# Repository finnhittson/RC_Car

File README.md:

# 9V Battery Power RC Car
This repo documents how to make an RC car and transmitter using 3D printted parts, a PIC16LF18325 microcontroller, nRF24L01 RF modules, a 9V battery to power the car and the transmitter, and other basic hardware components.

Table of contents:  
1. [Design Overview](##design-overview)
2. [Software](###software)
3. [Electrical](###electrical)
4. [Bill of Materials](##bill-of-materials)
## Design Overview
The three main components in building this car are the software, electrical, and the mechanical aspect of the car and controller. The following sections talks about each of these parts in detail.

### Software
Using the PIC16LF18326 as the microcontroller, the driver code was written exclusively in C. The driver code was programmed onto the PIC16 using the MPLAB SNAP and the MPLABX IDE. The software components are broken into the following three files:
1. `main.c`: runs main finite state machine responsible for executing high level transmitter/receiver instructions for controlling motors and servos for the receiver and reading analog control inputs for the trasmitter.
2. `spi.c`: helper SPI functions for transmitting and receiving messages to and from the nRF24L01 radio module.
3. `nRF24L01.c`: helper functions for configuring the nRF24L01 radio module using the `spi.c` functons.

Because this project is intended to be a workshop only one version of code or `main.c` file is written for simplicity. Therefore, for the `main.c` to differentiate between running transmitter code and receiver, a GPIO pin on the micro is dedicated for this indication. The pin under questions is RA5 (pin 2) from the tables below which descripe the pinout for the PIC16 in both the receiver and transmitter. If RA5 is pulled high, then the `main.c` executes transmitter code only. Similarly if RA5 is pulled low, then the `main.c` only executes receiver code. 

| Transmitter Pin Description |             |                |                 | | | Receiver Pin Description    |             |                |                 |
|-----------------------------|-------------|----------------|-----------------|-|-|-----------------------------|-------------|----------------|-----------------|
| **Pin Number**              | **Port**    | **Net Name**   | **Notes**       | | | **Pin Number**              | **Port**    | **Net Name**   | **Notes**       |
| 1                           | $V_{DD}$    | 3.3V           | power supply    | | | 1                           | $V_{DD}$    | 3.3V           | power supply    |
| 2                           | RA5         | 3.3V           | type select     | | | 2                           | RA5         | GND            | type select     |
| 3                           | RA4         | CSN            | SPI bus         | | | 3                           | RA4         | CSN            | SPI bus         |
| 4                           | RA3         | MCLR           | program/NC      | | | 4                           | RA3         | MCLR           | program/NC      |
| 5                           | RC5         | MOSI           | SPI bus         | | | 5                           | RC5         | CE             | radio enable    |
| 6                           | RC4         | SPEED          | pot input       | | | 6                           | RC4         | PWM5.1         | motor PWM       |
| 7                           | RC3         | STEER          | pot input       | | | 7                           | RC3         | PWM6           | servo PWM       |
|                             |             |                |                 | | |                             |             |                |                 |
| 8                           | RC2         | IRQ            | radio interrupt | | | 8                           | RC2         | PWM5           | motor PWM       |
| 9                           | RC1         | MISO           | SPI bus         | | | 9                           | RC1         | MISO           | SPI bus         |
| 10                          | RC0         | SCK            | SPI bus         | | | 10                          | RC0         | SCK            | SPI bus         |
| 11                          | RA2         | CE             | radio enable    | | | 11                          | RA2         | MOSI           | SPI bus         |
| 12                          | RA1         | STEER_TRIM     | pot input       | | | 12                          | RA1         | IRQ            | radio interrupt |
| 13                          | RA0         | LED            | status          | | | 13                          | RA0         | LIGHTS         | status          |
| 14                          | $V_{SS}$    | GND            | power supply    | | | 14                          | $V_{SS}$    | GND            | power supply    |

The following image shows the state machine executed on the transmitter PIC16. When the PIC16 detects its a transmitter then it starts the state machine with the inital state of *COLLECT_ADC_DATA*. In the *COLLECT_ADC_DATA* state, the PIC16 cycles through the three ADC ports to collect their value. Once complete, it transitions to the *TRANSMIT_ADC_DATA* state where it packages up this information into a packet and sents this information over the SPI bus to the nRF24L01 radio module. Once this is complete it then transitions to the *CLEAR_INTERRUPT* state. In this state the PIC16 is waiting for the interrupt line to go low which indicates a successful transmission to the receiver. From here the state machine then transitions to a *DONE* state where the hardware to read the analog pins is reinitialized and the process repeates itself after *DONE* transitions to *COLLECT_ADC_DATA*.

The transmission packet is 8 bytes long and has the following breakdown.
1. Byte 1 is the radio ID and is chosen by the user as an extra indentification method so that in the instance when the radio receives a packet from another RC car on the same channel, it will only execute the instructions if the packet come from a transmitter with the same ID.
2. Byte 2 is the high byte of the ADC conversion value for RC4. The PIC16 has a 10 bit ADC so it takes two bytes to store its value. It stores the eight LSB of the conversion in the first byte and the remaining two bits in the first two bits of the second byte.
3. Byte 3 is the low byte of the ADC conversion value for RC4.
4. Byte 4 is the high byte of the ADC conversion value for RC3.
5. Byte 5 is the low byte of the ADC conversion value for RC3.
6. Byte 6 is the high byte of the ADC conversion value for RA1.
7. Byte 7 is the low byte of the ADC conversion value for RA2.
8. Byte 8 is a checksum of all the bytes transmitted. The checksum is computed by summing all the bytes and subtracting the result from 0xFF. The result is transmitted and the receiver checks the checksum by summing every byte of the packet and if the result is 0xFF then no bits were corrupted or lost.

When the PIC16 detects is a receiver it starts the state machine in the *READ_RX*. In this state it waits until the interrupt line from the nRF24L01 radio module goes low which indicates that a packet has been received. From here it transitions to the *UPDATE_CONTROLS* state. In this state the PIC16 collects the packet from the nRF24L01 radio module, unpacks it, and updates the PWM signals for the servo and motor. Once complete it transitions back to the *READ_RX* state where it waits until the next packet is ready.

### Electrical
The receiver schematic is shown below. For the receiver, the PIC16LF18325 communicates with the nRF24L01 radio module through a SPI bus for receiving commands that are then decoded into a PWM signals for motor and servo control. The PIC16 also controls the motors and servo respectivly and was chosen for its small size, GPIO pin count, and packaging style. The L9110 h-bridge controls the motor and is a very basic h-bridge for driving small motors which make it perfect for this application. The LM2937 linear voltage regulator creates the 3.3V supply for the PIC16, nRF24L01 radio module, lights, and servo power. The lights part of the schematic act as the headlights of the car and are controlled by the PIC16 toggeling the 2N7000 mosfets. 

The transmitter schematic is shown below. In this instance the PIC16 commuicates with the nRF24L01 radio module to send commands for the receiver. The PIC16 also controls the status LED which indicates power and pairing status. The two modes of control are the two potentiometers which act as the cars accelerator and steering control. There is also one trim pot for the driver to tune the front steering axel so that the car does not drift left or right when driving straight.

### Mechanical

## Bill of Materials
| Transmitter Bill of Materials |                 |                |                         |
|-------------------------------|-----------------|----------------|-------------------------|
| **Component**                 | **Quantity**    | **Source**     | **Part Number**         |
| 9V battery                    | 1               | DigiKey        | 547-A1604BK210J-ND      |
| 0.1uF                         | 2               | DigiKey        | BC1084TR-ND             |
| 220uF                         | 1               | DigiKey        | 399-6122-ND             |
| 10uF                          | 1               | DigiKey        | 399-15738-ND            |
| LED                           | 2               | DigiKey        | 732-5016-ND             |
| 2N7000                        | 1               | DigiKey        | 4878-2N7000CT-ND        |
| 470                           | 2               | DigiKey        | CF14JT470RTR-ND         |
| 10k                           | 2               | DigiKey        | CF14JT10K0TR-ND         |
| 5k Control Pot                | 2               | DigiKey        | 2223-PT01-D115D-B502-ND |
| 5k Trim Pot                   | 1               | DigiKey        | 3386P-103LF-ND          |
| Power Switch                  | 1               | DigiKey        | EG1903-ND               |
| PIC16LF18326                  | 1               | DigiKey        | PIC16LF18326-I/P-ND     |
| nRF24L01 Radio Module         | 1               | AliExpress     | [nRF24L01](https://www.aliexpress.us/item/3256809251216534.html?src=google&pdp_npi=4%40dis%21USD%2139.51%2113.30%21%21%21%21%21%40%2112000049096107778%21ppc%21%21%21&snps=y&src=google&albch=shopping&acnt=752-015-9270&isdl=y&slnk=&plac=&mtctp=&albbt=Google_7_shopping&aff_platform=google&aff_short_key=_oDc8nzq&gclsrc=aw.ds&albagn=888888&ds_e_adid=&ds_e_matchtype=&ds_e_device=c&ds_e_network=x&ds_e_product_group_id=&ds_e_product_id=en3256809251216534&ds_e_product_merchant_id=5551326180&ds_e_product_country=US&ds_e_product_language=en&ds_e_product_channel=online&ds_e_product_store_id=&ds_url_v=2&albcp=22665133432&albag=&isSmbAutoCall=false&needSmbHouyi=false&gad_source=1&gad_campaignid=22655435907&gbraid=0AAAAA_eFwRAxECL3osierG--gtRFWs9HU&gclid=CjwKCAjw6P3GBhBVEiwAJPjmLhNZUnYiuj_4ZBXyOOlgW3nIMieQxQGaxVKJq8Jiy7AL6JZ8wVUovBoCkpIQAvD_BwE&gatewayAdapt=glo2usa) |
| LM2937                        | 1               | DigiKey        | LM2937ET-3.3/NOPB-ND    |

| Receiver Bill of Materials             |                 |                |                         |
|----------------------------------------|-----------------|----------------|-------------------------|
| **Component**                          | **Quantity**    | **Source**     | **Part Number**         |
| 9V battery connector                   | 1               | DigiKey        | 547-A1604BK210J-ND      |
| 0.1uF                                  | 2               | DigiKey        | BC1084TR-ND             |
| 220uF                                  | 1               | DigiKey        | 399-6122-ND             |
| 10uF                                   | 1               | DigiKey        | 399-15738-ND            |
| LED                                    | 2               | DigiKey        | 732-5016-ND             |
| 9g Servo                               | 2               | DigiKey        | 732-5016-ND             |
| 2N7000                                 | 1               | DigiKey        | 4878-2N7000CT-ND        |
| 470                                    | 2               | DigiKey        | CF14JT470RTR-ND         |
| 10k                                    | 2               | DigiKey        | CF14JT10K0TR-ND         |
| Power Switch                           | 1               | DigiKey        | EG1903-ND               |
| PIC16LF18326                           | 1               | DigiKey        | PIC16LF18326-I/P-ND     |
| nRF24L01 Radio Module                  | 1               | AliExpress     | [nRF24L01](https://www.aliexpress.us/item/3256809251216534.html?src=google&pdp_npi=4%40dis%21USD%2139.51%2113.30%21%21%21%21%21%40%2112000049096107778%21ppc%21%21%21&snps=y&src=google&albch=shopping&acnt=752-015-9270&isdl=y&slnk=&plac=&mtctp=&albbt=Google_7_shopping&aff_platform=google&aff_short_key=_oDc8nzq&gclsrc=aw.ds&albagn=888888&ds_e_adid=&ds_e_matchtype=&ds_e_device=c&ds_e_network=x&ds_e_product_group_id=&ds_e_product_id=en3256809251216534&ds_e_product_merchant_id=5551326180&ds_e_product_country=US&ds_e_product_language=en&ds_e_product_channel=online&ds_e_product_store_id=&ds_url_v=2&albcp=22665133432&albag=&isSmbAutoCall=false&needSmbHouyi=false&gad_source=1&gad_campaignid=22655435907&gbraid=0AAAAA_eFwRAxECL3osierG--gtRFWs9HU&gclid=CjwKCAjw6P3GBhBVEiwAJPjmLhNZUnYiuj_4ZBXyOOlgW3nIMieQxQGaxVKJq8Jiy7AL6JZ8wVUovBoCkpIQAvD_BwE&gatewayAdapt=glo2usa) |
| LM2937                                 | 1               | DigiKey        | LM2937ET-3.3/NOPB-ND    |
| L9110H                                 | 1               | DigiKey        | 1528-4489-ND            |

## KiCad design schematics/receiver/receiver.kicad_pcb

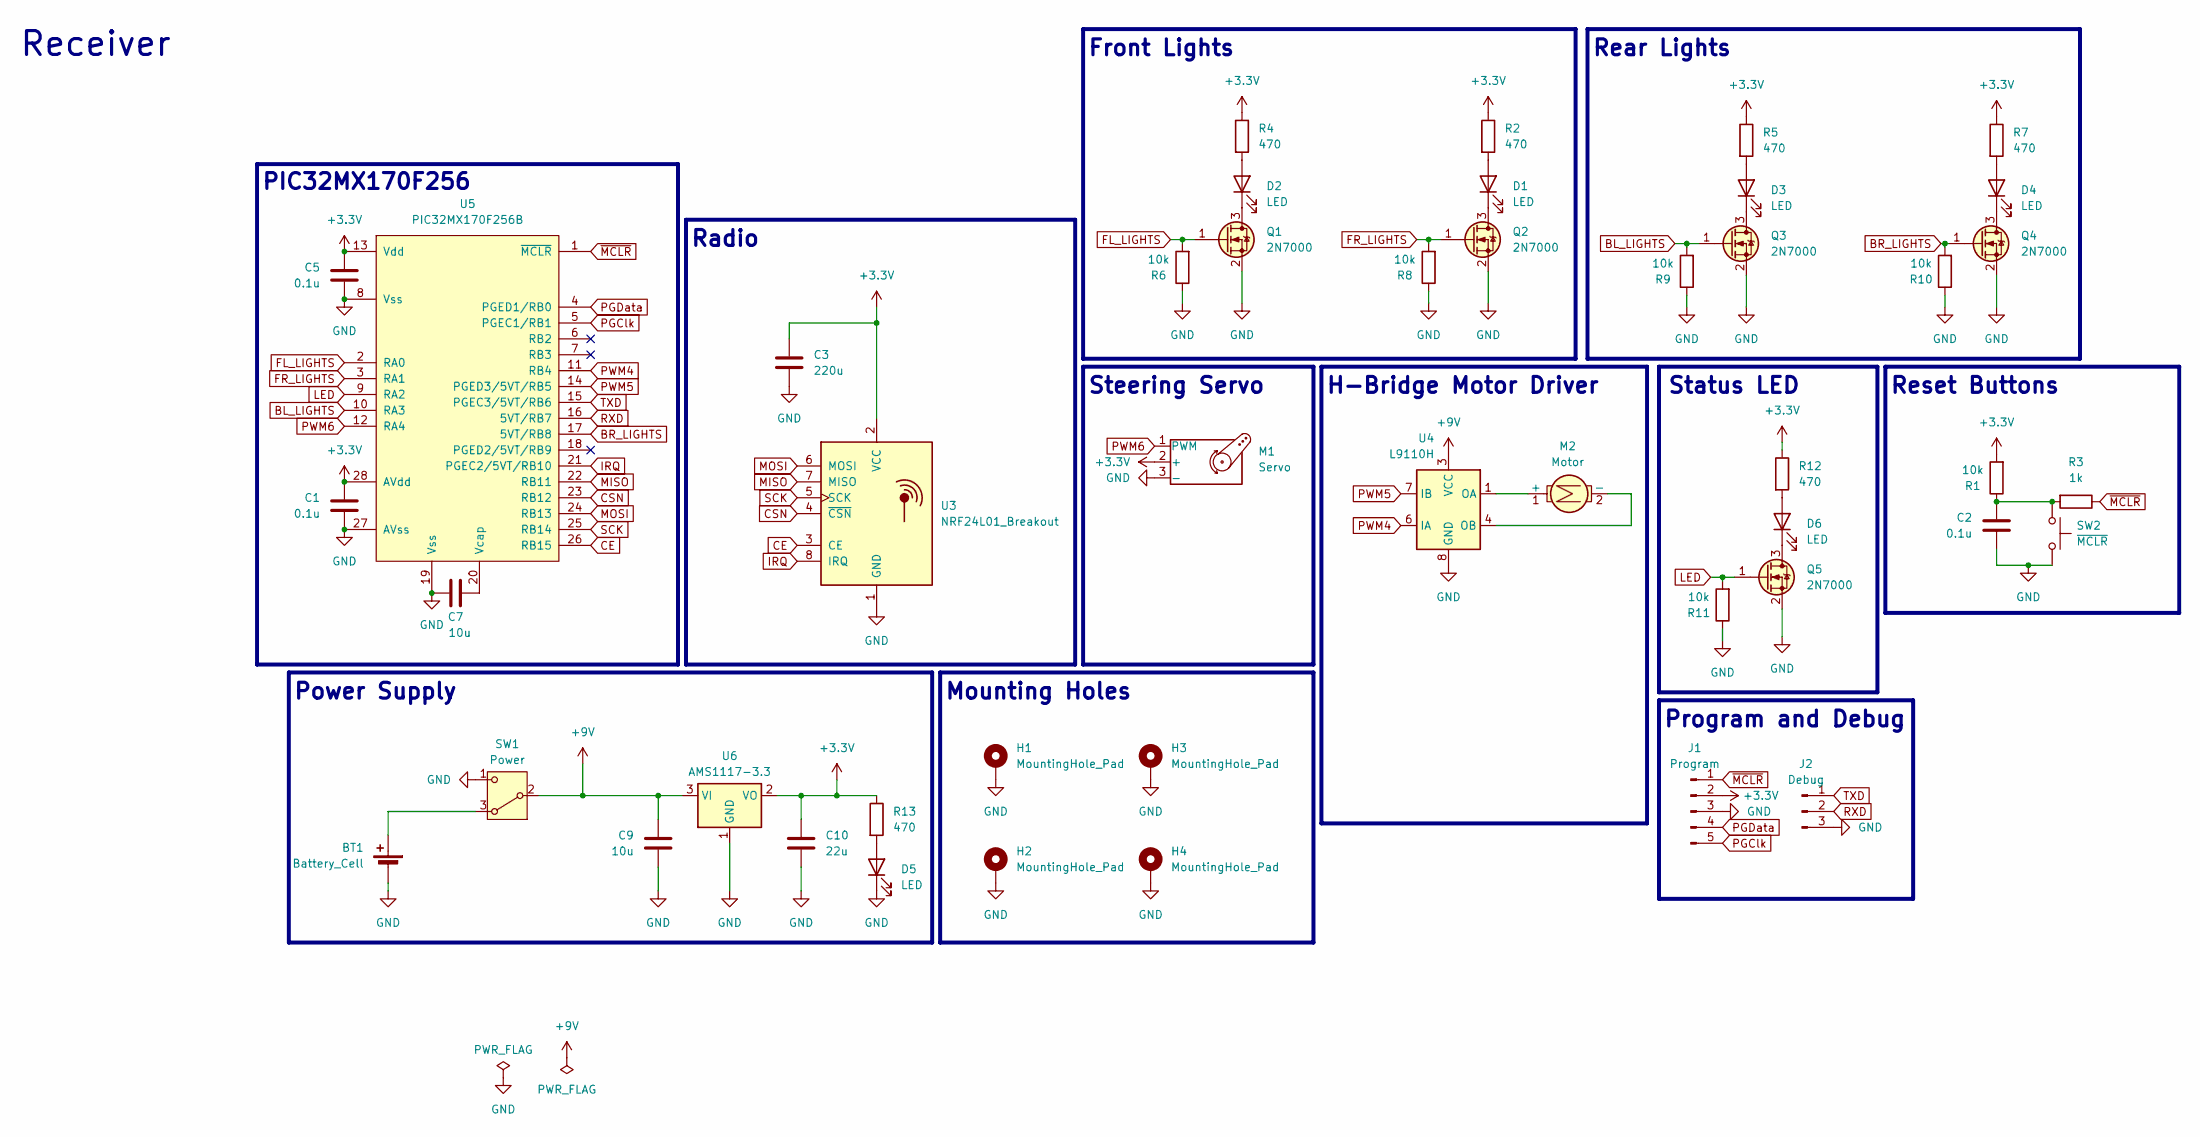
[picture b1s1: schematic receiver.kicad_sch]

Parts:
BT1: Battery_Cell; BAT_BH9VPC
C1, C2, C5: 0.1u; C_0402_1005Metric
C3: 220u; U2-K_NCH
C7: 10u; C_0402_1005Metric
C9: 10u; C_0805_2012Metric
C10: 22u; CP_EIA-2012-15_AVX-P
D1, D2, D3, D4: LED; PinSocket_1x02_P2.54mm_Vertical
D5, D6: LED; LED_0402_1005Metric
H1, H2, H3, H4: MountingHole_Pad; MountingHole_2.5mm_Pad_TopBottom
J1: Program; PinSocket_1x05_P2.54mm_Vertical
J2: Debug; PinSocket_1x03_P2.54mm_Vertical
M1: Servo; PinSocket_1x03_P2.54mm_Horizontal
M2: Motor; PinSocket_1x02_P2.54mm_Vertical
Q1, Q2, Q3, Q4, Q5: 2N7000; SOT-23
R1, R6, R8, R9, R10, R11: 10k; R_0402_1005Metric
R2, R4, R5, R7, R12, R13: 470; R_0402_1005Metric
R3: 1k; R_0402_1005Metric
SW1: Power; PinSocket_1x03_P2.54mm_Vertical
SW2: ~{MCLR}; SW_1825910-6-4
U3: NRF24L01_Breakout; nRF24L01_Breakout
U4: L9110H; DIP-8_W7.62mm_Socket
U5: PIC32MX170F256B; SSOP28_MC_MCH
U6: AMS1117-3.3; SOT-223-3_TabPin2

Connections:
+3.3V: C1.2, C3.1, C5.2, C10.1, J1.2, M1.2 (+), R1.2, R2.1, R4.1, R5.1, R7.1, R12.1, R13.1, U3.2 (VCC), U5.13 (Vdd), U5.28 (AVdd), U6.2 (VO)
+9V: C9.1, SW1.2 (B), U4.2 (VCC), U4.3 (VCC), U6.3 (VI)
BL_LIGHTS: Q3.1 (G), R9.2, U5.10 (RA3)
BR_LIGHTS: Q4.1 (G), R10.2, U5.17 (5VT/RB8)
CE: U3.3 (CE), U5.26 (RB15)
CSN: U3.4 (~CSN), U5.23 (RB12)
FL_LIGHTS: Q1.1 (G), R6.2, U5.2 (RA0)
FR_LIGHTS: Q2.1 (G), R8.2, U5.3 (RA1)
GND: BT1.2 (-), C1.1, C2.1, C3.2, C5.1, C7.2, C9.2, C10.2, D5.1 (K), H1.1, H2.1, H3.1, H4.1, J1.3, J2.3, M1.3 (-), Q1.2 (S), Q2.2 (S), Q3.2 (S), Q4.2 (S), Q5.2 (S), R6.1, R8.1, R9.1, R10.1, R11.1, SW1.1 (C), SW2.3, SW2.4, U3.1 (GND), U4.5 (GND), U4.8 (GND), U5.8 (Vss), U5.19 (Vss), U5.27 (AVss), U6.1 (GND)
IRQ: U3.8 (IRQ), U5.21 (PGEC2/5VT/RB10)
LED: Q5.1 (G), R11.2, U5.9 (RA2)
MISO: U3.7 (MISO), U5.22 (RB11)
MOSI: U3.6 (MOSI), U5.24 (RB13)
unnamed: BT1.1 (+), SW1.3 (A)
unnamed: C2.2, R1.1, R3.2, SW2.1, SW2.2
unnamed: D1.2 (A), R2.2
unnamed: D1.1 (K), Q2.3 (D)
unnamed: D2.2 (A), R4.2
unnamed: D2.1 (K), Q1.3 (D)
unnamed: D3.2 (A), R5.2
unnamed: D3.1 (K), Q3.3 (D)
unnamed: D4.2 (A), R7.2
unnamed: D4.1 (K), Q4.3 (D)
unnamed: D5.2 (A), R13.2
unnamed: D6.2 (A), R12.2
unnamed: D6.1 (K), Q5.3 (D)
unnamed: M2.1 (+), U4.1 (OA)
unnamed: M2.2 (-), U4.4 (OB)
unnamed: C7.1, U5.20 (Vcap)
PGClk: J1.5, U5.5 (PGEC1/RB1)
PGData: J1.4, U5.4 (PGED1/RB0)
PWM4: U4.6 (IA), U5.11 (RB4)
PWM5: U4.7 (IB), U5.14 (PGED3/5VT/RB5)
PWM6: M1.1 (PWM), U5.12 (RA4)
RXD: J2.2, U5.16 (5VT/RB7)
SCK: U3.5 (SCK), U5.25 (RB14)
TXD: J2.1, U5.15 (PGEC3/5VT/RB6)
~MCLR: J1.1, R3.1, U5.1 (~MCLR)

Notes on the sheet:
Program and Debug
Power Supply
Rear Lights
Front Lights
PIC32MX170F256
Radio
Status LED
Receiver
H-Bridge Motor Driver
Reset Buttons
Steering Servo
Mounting Holes

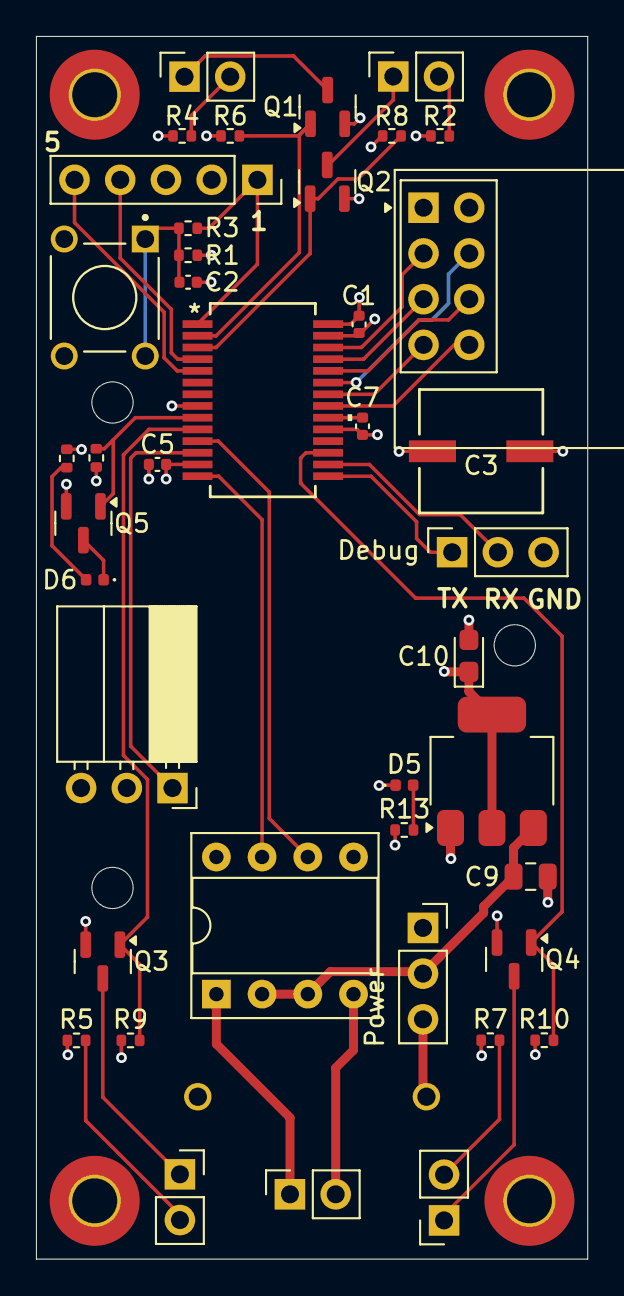
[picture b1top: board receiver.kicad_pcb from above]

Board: 4 copper layers, 30.6 x 67.9 mm, 46 parts (1 on the bottom side), 38 nets.

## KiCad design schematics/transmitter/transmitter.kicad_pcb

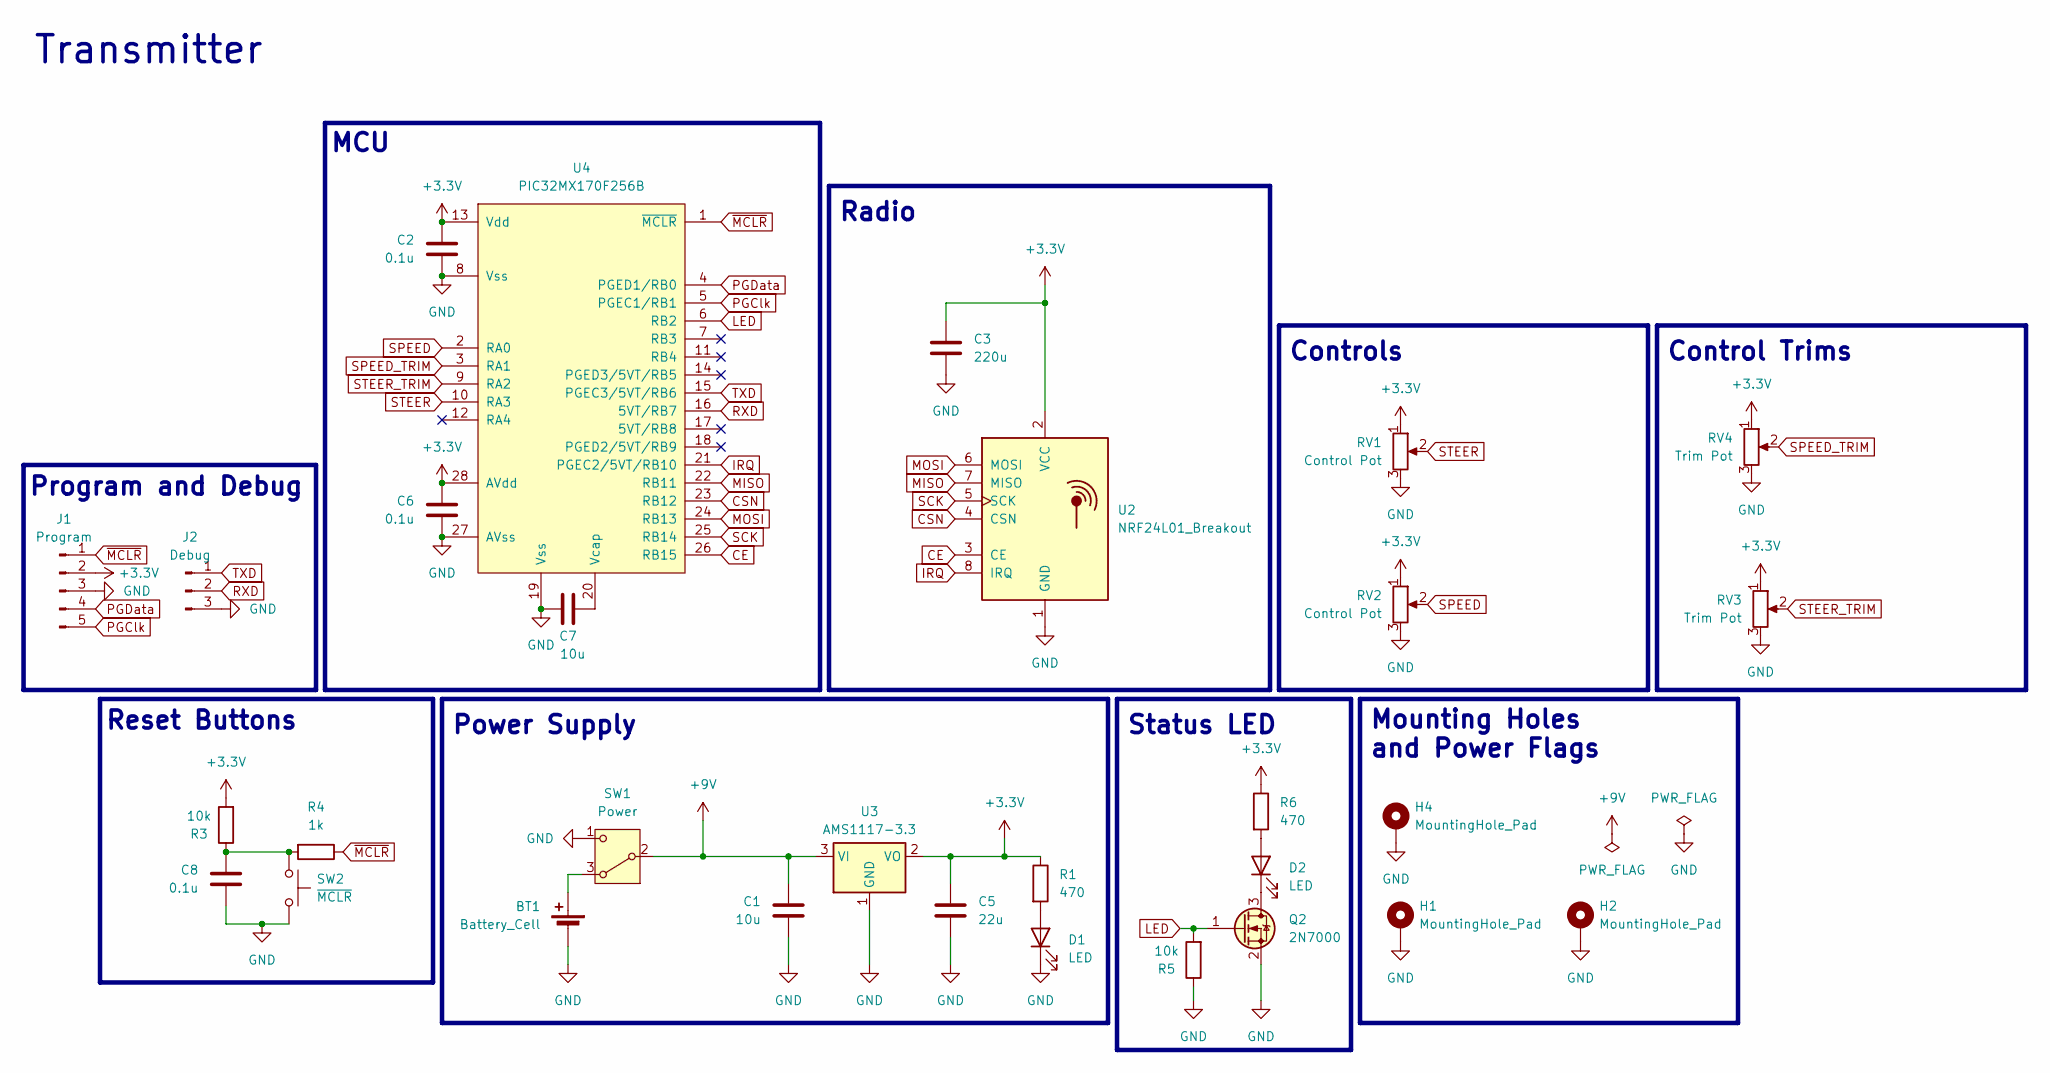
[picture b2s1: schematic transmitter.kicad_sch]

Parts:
BT1: Battery_Cell; PinSocket_1x02_P2.54mm_Vertical
C1: 10u; C_0805_2012Metric
C2, C6, C8: 0.1u; C_0402_1005Metric
C3: 220u; U2-K_NCH
C5: 22u; CP_EIA-2012-15_AVX-P
C7: 10u; C_0402_1005Metric
D1, D2: LED; LED_0402_1005Metric
H1, H2, H4: MountingHole_Pad; MountingHole_2.5mm_Pad_TopBottom
J1: Program; PinSocket_1x05_P2.54mm_Vertical
J2: Debug; PinSocket_1x03_P2.54mm_Vertical
Q2: 2N7000; SOT-23
R1, R6: 470; R_0402_1005Metric
R3, R5: 10k; R_0402_1005Metric
R4: 1k; R_0402_1005Metric
RV1, RV2: Control Pot; TRIM_PT01-D115D-B502
RV3, RV4: Trim Pot; Potentiometer_Bourns_3386P_Vertical
SW1: Power; PinSocket_1x03_P2.54mm_Vertical
SW2: ~{MCLR}; SW_1825910-6-4
U2: NRF24L01_Breakout; nRF24L01_Breakout
U3: AMS1117-3.3; SOT-223-3_TabPin2
U4: PIC32MX170F256B; SSOP28_MC_MCH

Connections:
+3.3V: C2.2, C3.1, C5.1, C6.2, J1.2, R1.1, R3.2, R6.1, RV1.1, RV2.1, RV3.1, RV4.1, U2.2 (VCC), U3.2 (VO), U4.13 (Vdd), U4.28 (AVdd)
+9V: C1.1, SW1.2 (B), U3.3 (VI)
CE: U2.3 (CE), U4.26 (RB15)
CSN: U2.4 (CSN), U4.23 (RB12)
GND: BT1.2 (-), C1.2, C2.1, C3.2, C5.2, C6.1, C7.2, C8.1, D1.1 (K), H1.1, H2.1, H4.1, J1.3, J2.3, Q2.2 (S), R5.1, RV1.3, RV1.S1, RV1.S2, RV2.3, RV2.S1, RV2.S2, RV3.3, RV4.3, SW1.1 (C), SW2.3, SW2.4, U2.1 (GND), U3.1 (GND), U4.8 (Vss), U4.19 (Vss), U4.27 (AVss)
IRQ: U2.8 (IRQ), U4.21 (PGEC2/5VT/RB10)
LED: Q2.1 (G), R5.2, U4.6 (RB2)
MISO: U2.7 (MISO), U4.22 (RB11)
MOSI: U2.6 (MOSI), U4.24 (RB13)
unnamed: BT1.1 (+), SW1.3 (A)
unnamed: C8.2, R3.1, R4.2, SW2.1, SW2.2
unnamed: D1.2 (A), R1.2
unnamed: D2.2 (A), R6.2
unnamed: D2.1 (K), Q2.3 (D)
unnamed: C7.1, U4.20 (Vcap)
PGClk: J1.5, U4.5 (PGEC1/RB1)
PGData: J1.4, U4.4 (PGED1/RB0)
RXD: J2.2, U4.16 (5VT/RB7)
SCK: U2.5 (SCK), U4.25 (RB14)
SPEED: RV2.2, U4.2 (RA0)
SPEED_TRIM: RV4.2, U4.3 (RA1)
STEER: RV1.2, U4.10 (RA3)
STEER_TRIM: RV3.2, U4.9 (RA2)
TXD: J2.1, U4.15 (PGEC3/5VT/RB6)
~MCLR: J1.1, R4.1, U4.1 (~MCLR)

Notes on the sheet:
Control Trims
Power Supply
Radio
Status LED
MCU
Mounting Holes and Power Flags
Reset Buttons
Controls
Program and Debug
Transmitter

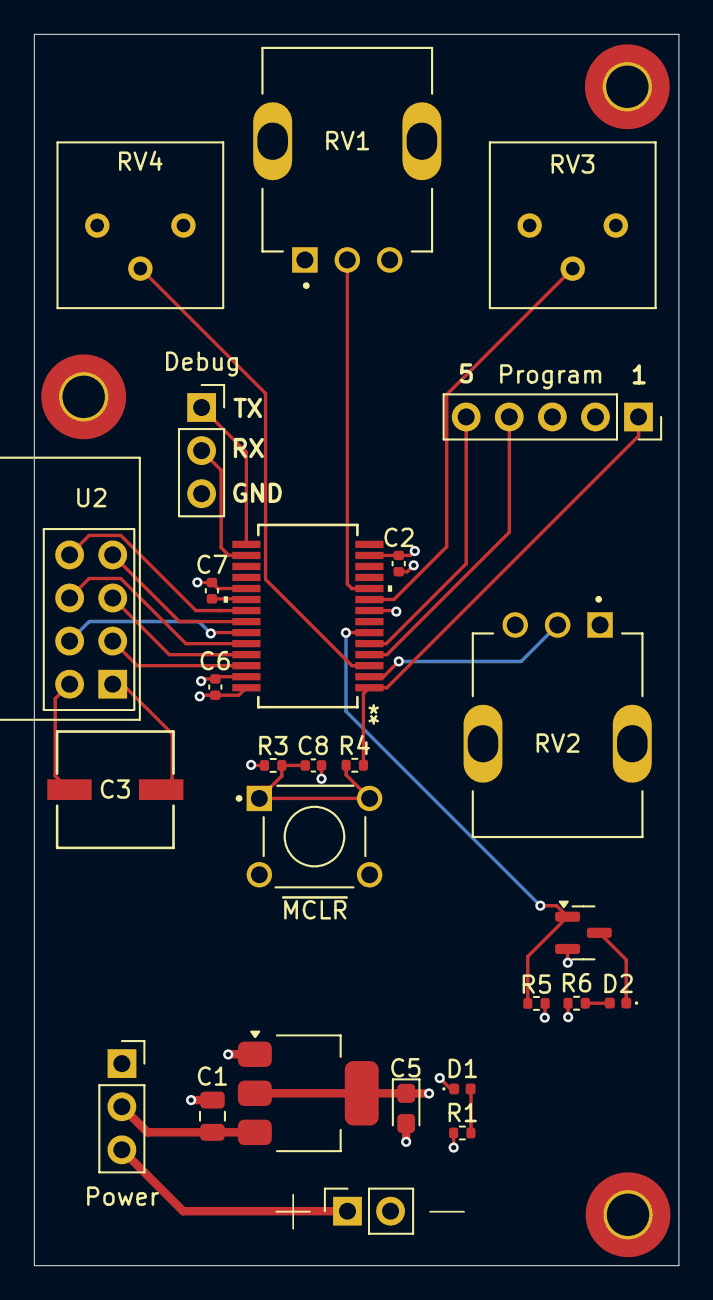
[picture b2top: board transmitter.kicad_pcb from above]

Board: 4 copper layers, 38.0 x 72.6 mm, 30 parts (0 on the bottom side), 25 nets.

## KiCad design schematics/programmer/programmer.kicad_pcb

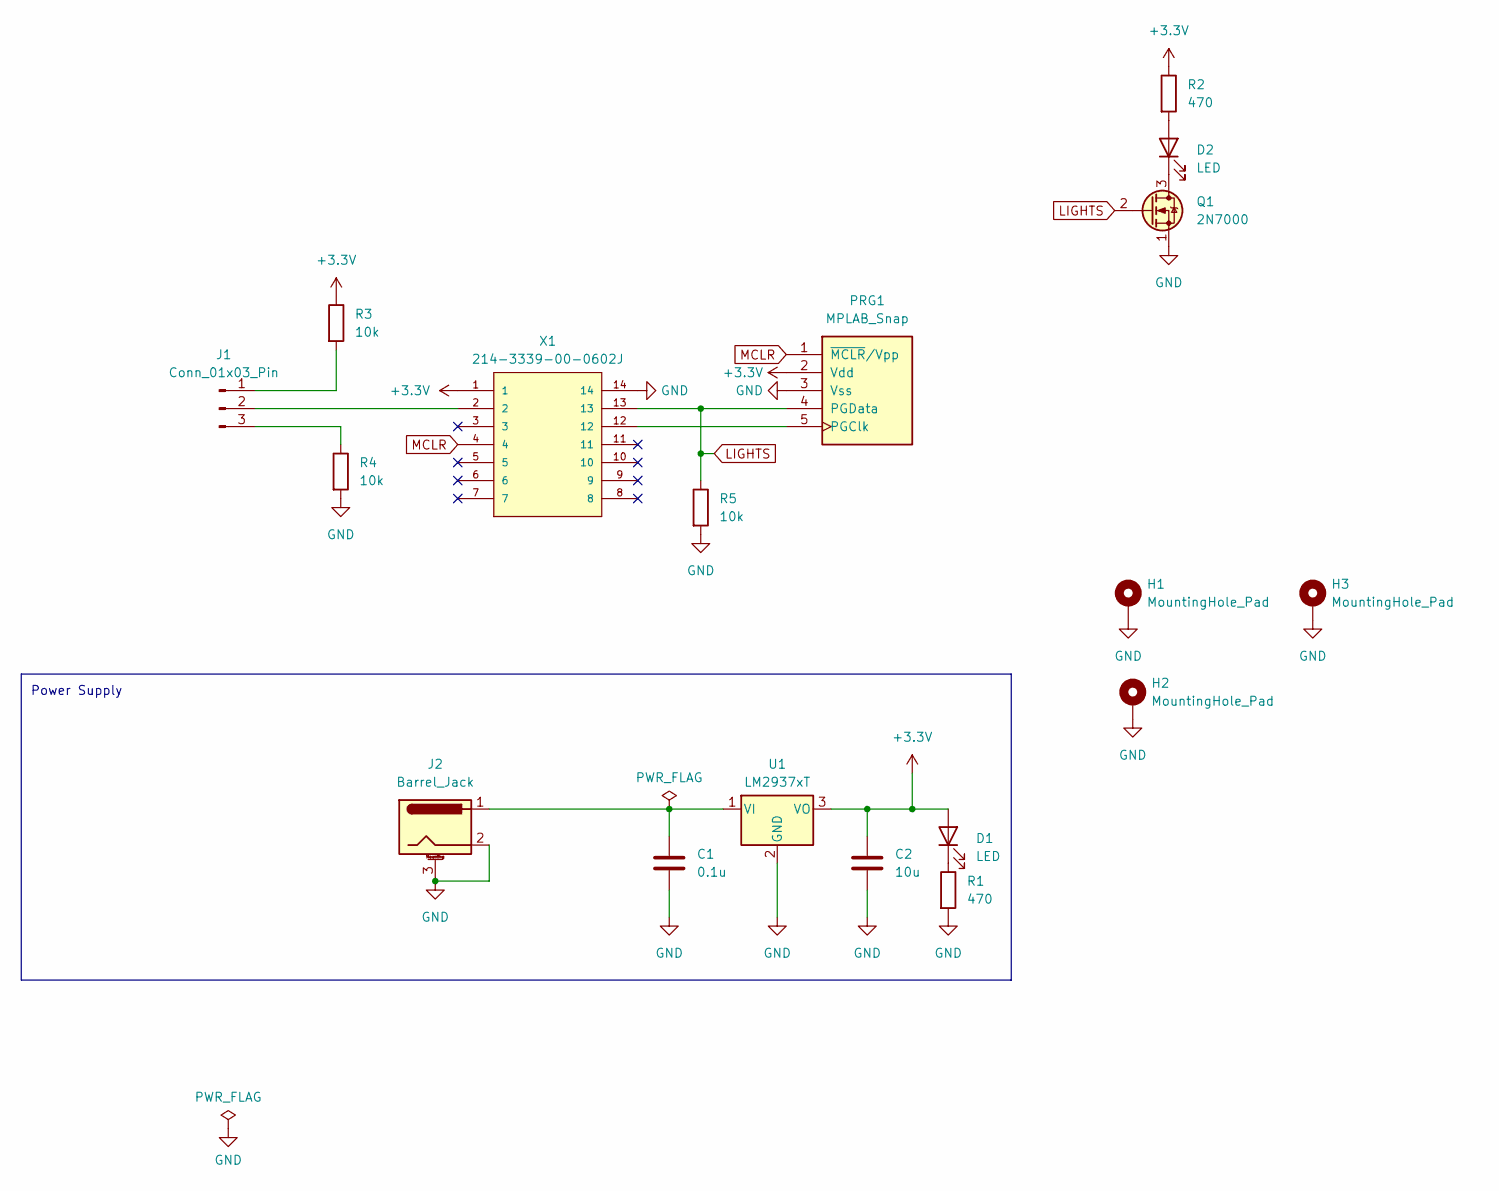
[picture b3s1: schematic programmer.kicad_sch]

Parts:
C1: 0.1u; CP_Radial_D5.0mm_P2.50mm
C2: 10u; CP_Radial_D5.0mm_P2.50mm
D1, D2: LED; LED_D5.0mm
H1, H2, H3: MountingHole_Pad; MountingHole_2.5mm_Pad_TopBottom
J1: Conn_01x03_Pin; PinSocket_1x03_P2.54mm_Vertical
J2: Barrel_Jack; BarrelJack_Horizontal
PRG1: MPLAB_Snap; PinSocket_1x08_P2.54mm_Vertical
Q1: 2N7000; TO-92_Inline_Wide
R1, R2: 470; R_Axial_DIN0204_L3.6mm_D1.6mm_P7.62mm_Horizontal
R3, R4, R5: 10k; R_Axial_DIN0204_L3.6mm_D1.6mm_P7.62mm_Horizontal
U1: LM2937xT; TO-220-3_Horizontal_TabDown
X1: 214-3339-00-0602J; 3M_214-3339-00-0602J

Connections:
+3.3V: C2.1, D1.2 (A), PRG1.2 (Vdd), R2.1, R3.1, U1.3 (VO), X1.1
GND: C1.2, C2.2, H1.1, H2.1, H3.1, J2.2, J2.3 (MountPin), PRG1.3 (Vss), Q1.1 (S), R1.2, R4.2, R5.2, U1.2 (GND), X1.14
LIGHTS: PRG1.4 (PGData), Q1.2 (G), R5.1, X1.13
MCLR: PRG1.1 (~MCLR/Vpp), X1.4
unnamed: D1.1 (K), R1.1
unnamed: D2.2 (A), R2.2
unnamed: D2.1 (K), Q1.3 (D)
unnamed: J1.1, R3.2
unnamed: J1.2, X1.2
unnamed: J1.3, R4.1
unnamed: PRG1.5 (PGClk), X1.12
unnamed: C1.1, J2.1, U1.1 (VI)

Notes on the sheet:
Power Supply

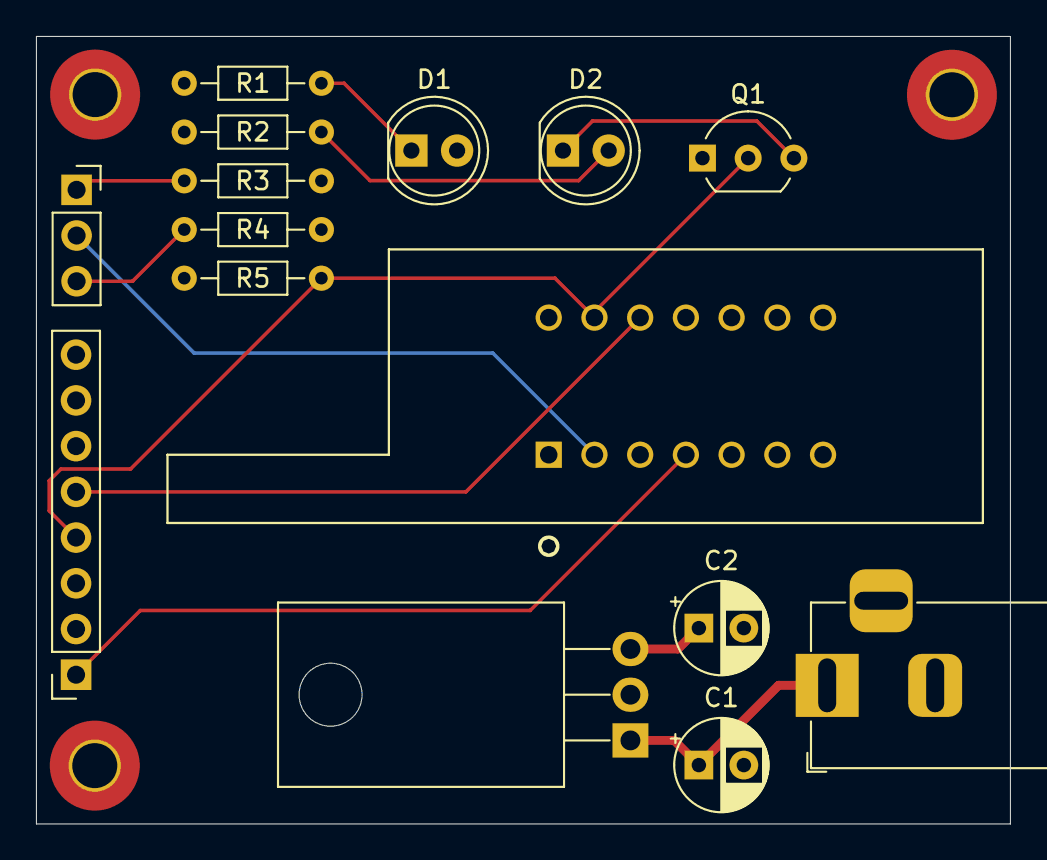
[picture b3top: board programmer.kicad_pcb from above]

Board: 4 copper layers, 54.1 x 43.7 mm, 18 parts (0 on the bottom side), 12 nets.

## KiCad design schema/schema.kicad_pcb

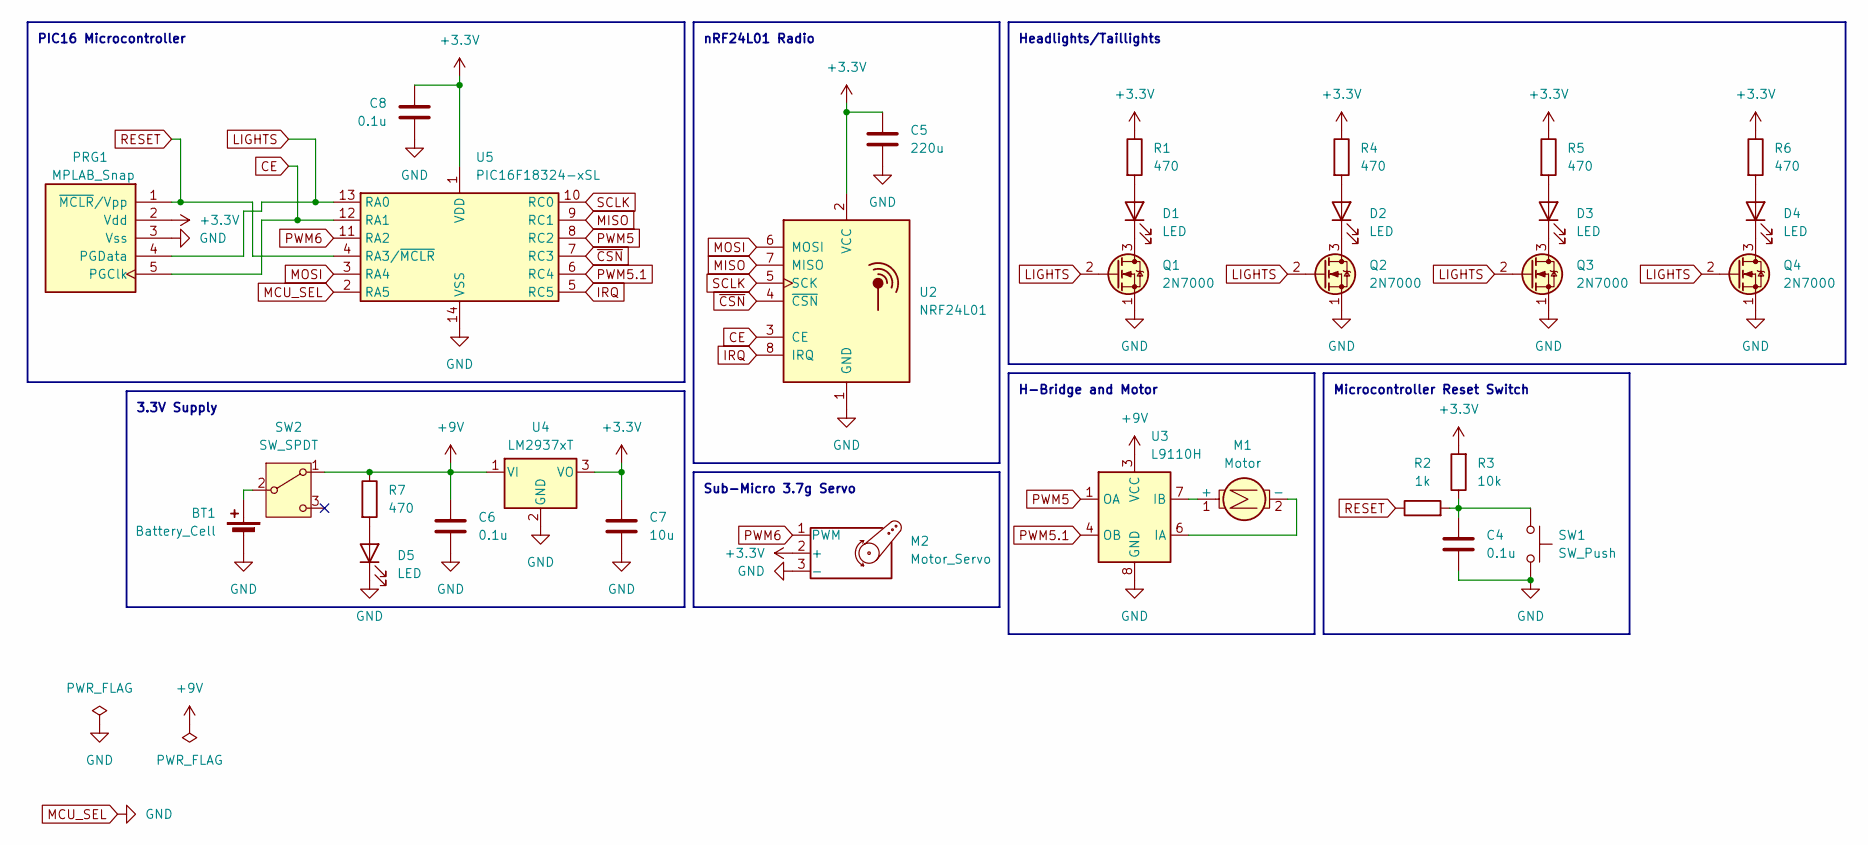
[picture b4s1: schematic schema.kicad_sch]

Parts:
BT1: Battery_Cell; BAT_BH9VPC
C4, C6, C8: 0.1u; C_Rect_L4.0mm_W2.5mm_P2.50mm
C5: 220u; C_Rect_L4.0mm_W2.5mm_P2.50mm
C7: 10u; C_Rect_L4.0mm_W2.5mm_P2.50mm
D1, D2, D3, D4, D5: LED; LED_D5.0mm
M1: Motor; PinSocket_1x02_P2.54mm_Vertical
M2: Motor_Servo; PinSocket_1x03_P2.54mm_Vertical
PRG1: MPLAB_Snap; PinSocket_1x05_P2.54mm_Vertical
Q1, Q2, Q3, Q4: 2N7000; TO-92_Inline_Wide
R1, R4, R5, R6, R7: 470; R_Axial_DIN0204_L3.6mm_D1.6mm_P7.62mm_Horizontal
R2: 1k; R_Axial_DIN0204_L3.6mm_D1.6mm_P7.62mm_Horizontal
R3: 10k; R_Axial_DIN0204_L3.6mm_D1.6mm_P7.62mm_Horizontal
SW1: SW_Push; SW_TS02-66-60-BK-160-LCR-D
SW2: SW_SPDT; SW_EG1218
U2: NRF24L01; nRF24L01_Breakout
U3: L9110H; DIP-8_W7.62mm_Socket
U4: LM2937xT; TO-220-3_Vertical
U5: PIC16F18324-xSL; CERDIP-14_W7.62mm_SideBrazed

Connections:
+3.3V: C5.1, C7.1, C8.2, M2.2 (+), PRG1.2 (Vdd), R1.1, R3.2, R4.1, R5.1, R6.1, U2.2 (VCC), U4.3 (VO), U5.1 (VDD)
+9V: C6.1, R7.1, SW2.1 (A), U3.2 (VCC), U3.3 (VCC), U4.1 (VI)
CE: PRG1.5 (PGClk), U2.3 (CE), U5.12 (RA1)
IRQ: U2.8 (IRQ), U5.5 (RC5)
LIGHTS: PRG1.4 (PGData), Q1.2 (G), Q2.2 (G), Q3.2 (G), Q4.2 (G), U5.13 (RA0)
MCU_SEL: BT1.2 (-), C4.2, C5.2, C6.2, C7.2, C8.1, D5.1 (K), M2.3 (-), PRG1.3 (Vss), Q1.1 (S), Q2.1 (S), Q3.1 (S), Q4.1 (S), SW1.3, SW1.4, U2.1 (GND), U3.5 (GND), U3.8 (GND), U4.2 (GND), U5.2 (RA5), U5.14 (VSS)
MISO: U2.7 (MISO), U5.9 (RC1)
MOSI: U2.6 (MOSI), U5.3 (RA4)
unnamed: BT1.1 (+), SW2.2 (B)
unnamed: C4.1, R2.2, R3.1, SW1.1, SW1.2
unnamed: D1.2 (A), R1.2
unnamed: D1.1 (K), Q1.3 (D)
unnamed: D2.2 (A), R4.2
unnamed: D2.1 (K), Q2.3 (D)
unnamed: D3.2 (A), R5.2
unnamed: D3.1 (K), Q3.3 (D)
unnamed: D4.2 (A), R6.2
unnamed: D4.1 (K), Q4.3 (D)
unnamed: D5.2 (A), R7.2
unnamed: M1.1 (+), U3.7 (IB)
unnamed: M1.2 (-), U3.6 (IA)
PWM5: U3.1 (OA), U5.8 (RC2)
PWM5.1: U3.4 (OB), U5.6 (RC4)
PWM6: M2.1 (PWM), U5.11 (RA2)
RESET: PRG1.1 (~MCLR/Vpp), R2.1, U5.4 (RA3/~MCLR)
SCLK: U2.5 (SCK), U5.10 (RC0)
~CSN: U2.4 (~CSN), U5.7 (RC3)

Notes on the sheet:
Microcontroller Reset Switch
Headlights/Taillights
PIC16 Microcontroller
3.3V Supply
Sub-Micro 3.7g Servo
nRF24L01 Radio
H-Bridge and Motor

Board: 4 copper layers, 31 parts (1 on the bottom side), 27 nets, no tracks yet.

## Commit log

2025-07-04 Begin schematic for rc car
2025-07-04 Start mplabx code project
2025-07-04 Added set tx/rx address functionality
2025-07-05 Able to transmit. Does not recieve
2025-07-08 Working transmitting code
2025-07-09 Clean up working TX code
2025-07-09 Working receiver code
2025-07-09 Clean up code and move defines to header
2025-07-12 Update schematic with new microcontroller
2025-07-14 Add ISR to handle IRQ on nRF24L01
2025-07-15 Working receiver code with ISR
2025-07-16 Working RX/TX code on PIC32's
2025-07-19 Add datasheets
2025-07-19 Update schematic. Remote motor control working
2025-07-20 Add servo pwm
2025-07-20 Restructured and moved functions to separate files
2025-07-20 Removed overkill functions
2025-08-05 Update schematic to use PIC16 from PIC32
2025-08-05 Begin porting code from PIC32 to PIC16
2025-08-05 Update schematics 3d models for rendering
2025-08-07 Add ADC channel init
2025-08-07 Add switch to schema
2025-08-25 Change pinout on pic16 in schematic
2025-08-25 Begin transmiter schematic
2025-08-25 Correct faulty SPI code and add transmitter FSM
2025-08-25 Remove result passing network; unnecessary
2025-08-29 Refactors schematics
2025-08-29 Remove out of data schematics
2025-08-29 Remove unnecessary devices
2025-08-29 Remove out of date code
2025-08-29 Add schematic titles
2025-08-29 Create pin description document for TX and RX
2025-08-29 Change mcu type select to be pull down for RX board
2025-08-29 Add pull up for TX mcu select
2025-08-30 Working motor and servo driver code
2025-08-31 Remove rear LEDs and move hbridge away from radio
2025-08-31 Rearrange for more room for screws
2025-09-01 Created programming board. Schematic needs cleaning up
2025-09-01 Add pull down resistor
2025-09-01 Add pull down resistor for LED control on receiver board
2025-09-01 Add pull down for lights on transmitter board
2025-09-02 Remove trim pot, seems unnecessary
2025-09-14 Begin master bill of materials
2025-09-14 Remove programing ports and reset btn from final boards
2025-09-22 Updated switch with better 3d model
2025-09-24 Add trim pot to transmitter
2025-09-25 Update schematic backups
2025-09-25 Create gerber files and order
2025-10-04 Make receiver schematic more readable and add images
2025-10-04 Crop receiver schematic
2025-10-04 Start electrical section for readme
2025-10-04 Update schematics and their images
2025-10-04 Create state machines
2025-10-04 Create visual for comms protocol
2025-10-04 Rename state machine folder
2025-10-04 Rename state diagram files
2025-10-04 Update BOM for transmitter
2025-10-07 Update images
2025-10-07 Add more comments
2025-10-07 Combine main image
2025-10-07 Update main image
2025-10-07 Update images so they have white background
2025-12-23 Update bom
2025-12-23 Update xml files
2026-01-05 Mark changes on kicad
